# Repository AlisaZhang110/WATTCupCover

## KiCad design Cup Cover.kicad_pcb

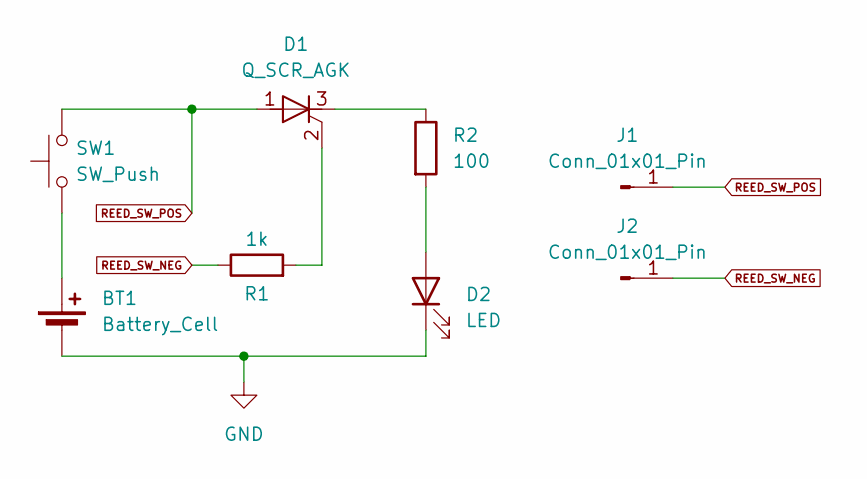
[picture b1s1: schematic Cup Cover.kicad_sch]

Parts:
BT1: Battery_Cell; BAT_BAT-HLD-003-SMT
D1: Q_SCR_AGK; SOT-23-3
D2: LED; LED_1206_3216Metric
J1, J2: Conn_01x01_Pin; ADAM-TECH_PH1-01-UA
R1: 1k; R_1206_3216Metric
R2: 100; RESC3116X65N
SW1: SW_Push; SW_TS10-63-26-BE-250-SMT-TR

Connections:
GND: BT1.N (-), D2.1 (K)
unnamed: BT1.P1 (+), SW1.1
unnamed: D1.2 (G), R1.2
unnamed: D1.3 (K), R2.1
unnamed: D2.2 (A), R2.2
REED_SW_NEG: J2.1, R1.1
REED_SW_POS: D1.1 (A), J1.1, SW1.2

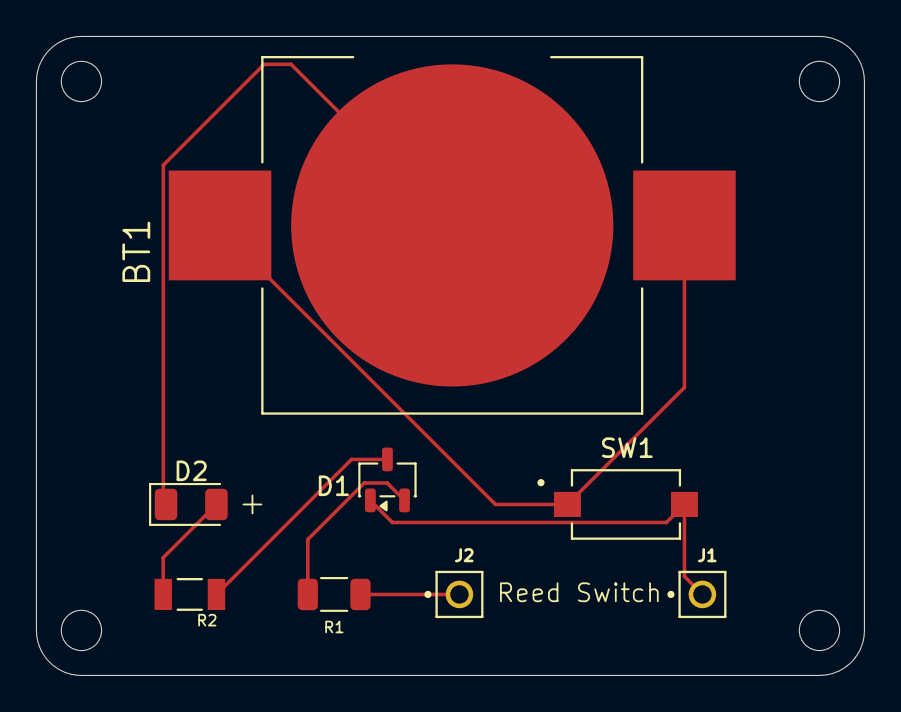
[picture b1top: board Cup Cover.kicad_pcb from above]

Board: 2 copper layers, 46.0 x 35.5 mm, 8 parts (0 on the bottom side), 7 nets.

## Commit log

2026-02-19 PCB in progress
2026-02-20 board review 1 (battery footp, reed sw)
2026-02-20 2/20 Routed PCB
2026-02-22 ground plane
